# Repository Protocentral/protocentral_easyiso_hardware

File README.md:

ProtoCentral easyISO — Isolated Qwiic Adapter
==============================================

easyISO galvanically isolates a Qwiic / STEMMA QT I²C link — data and power — so a body-connected
sensor never shares a ground with a mains-powered computer.

* **I²C isolator:** TI ISO1640 (8-pin SOIC), bidirectional SDA/SCL, hot-swappable, up to 1.7 MHz
* **Isolated power:** MPS MIE1W0505BGLVH isolated DC-DC module, 3.3 V out (about 75 mA)
* **Connectors:** one Qwiic port and one 0.1" 4-pin header (SCL, SDA, VCC, GND) on each side
* **Pull-ups:** 10 kΩ on SDA and SCL, on both sides
* **Board:** 33 × 18.7 mm, 2-layer, 4 × M2 mounting holes

The voltage ratings above are the manufacturers' component ratings. easyISO is a development tool,
not a certified medical isolation barrier.

Repository contents
-------------------
* **/hardware** — KiCad project (`easyISO.kicad_pro`, `.kicad_sch`, `.kicad_pcb`) and the schematic
  PDF (`pc_easyiso_v1_schematic.pdf`)

Revisions
---------
| Revision | Date | Notes |
|---|---|---|
| v1 | 2026-08 | First release |

License Information
===================

Hardware
--------
**All hardware is released under the [CERN-OHL-P v2](https://ohwr.org/cern_ohl_p_v2.txt)** license.

This source describes Open Hardware and is licensed under the CERN-OHL-P v2.

You may redistribute and modify this documentation and make products using it under the terms of
the CERN-OHL-P v2 (https://cern.ch/cern-ohl). This documentation is distributed WITHOUT ANY EXPRESS
OR IMPLIED WARRANTY, INCLUDING OF MERCHANTABILITY, SATISFACTORY QUALITY AND FITNESS FOR A
PARTICULAR PURPOSE. Please see the CERN-OHL-P v2 for applicable conditions.

Documentation
-------------
**All documentation is released under [Creative Commons Share-alike 4.0 International](http://creativecommons.org/licenses/by-sa/4.0/).**

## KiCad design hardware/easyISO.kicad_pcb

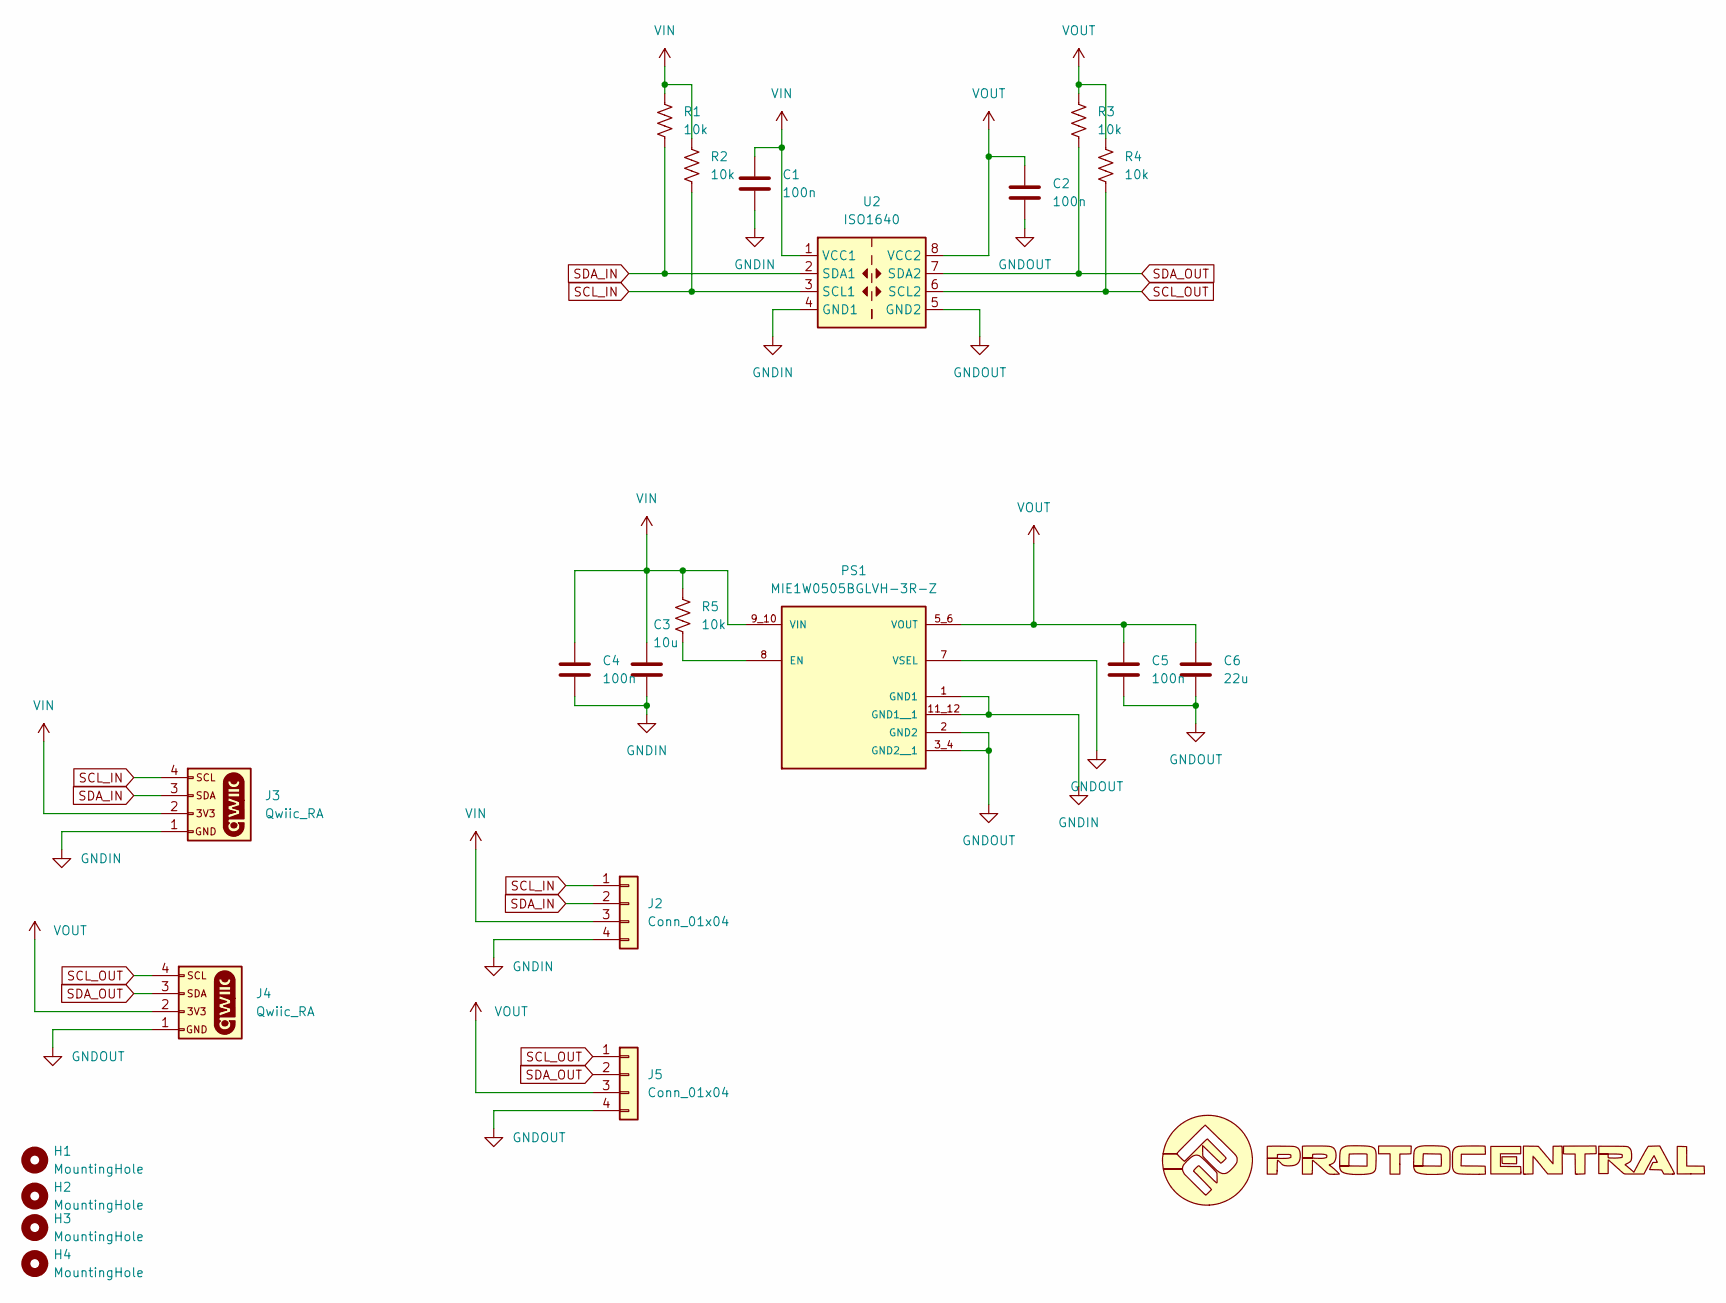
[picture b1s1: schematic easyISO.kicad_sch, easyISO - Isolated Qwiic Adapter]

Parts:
C1, C2, C4, C5: 100n; C_0402_1005Metric
C3: 10u; C_0805_2012Metric
C6: 22u; C_0805_2012Metric
H1, H2, H3, H4: MountingHole; MountingHole_2.2mm_M2
J2, J5: Conn_01x04; PinHeader_1x04_P2.54mm_Vertical
J3, J4: Qwiic_RA; JST_SH_SM04B-SRSS-TB_1x04-1MP_P1.00mm_Horizontal
PS1: MIE1W0505BGLVH-3R-Z; CONV_MIE1W0505BGLVH-3R-Z; PARTREV 0.8
R1, R2, R3, R4, R5: 10k; R_0402_1005Metric
U1: LOGO
U2: ISO1640; SOIC-8_3.9x4.9mm_P1.27mm

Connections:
GNDIN: C1.2, C3.2, C4.2, J2.4, J3.1, PS1.1 (GND1), PS1.11_12 (GND1__1), U2.4 (GND1)
GNDOUT: C2.2, C5.2, C6.2, J4.1, J5.4, PS1.2 (GND2), PS1.3_4 (GND2__1), PS1.7 (VSEL), U2.5 (GND2)
unnamed: PS1.8 (EN), R5.2
SCL_IN: J2.1, J3.4, R2.2, U2.3 (SCL1)
SCL_OUT: J4.4, J5.1, R4.2, U2.6 (SCL2)
SDA_IN: J2.2, J3.3, R1.2, U2.2 (SDA1)
SDA_OUT: J4.3, J5.2, R3.2, U2.7 (SDA2)
VIN: C1.1, C3.1, C4.1, J2.3, J3.2, PS1.9_10 (VIN), R1.1, R2.1, R5.1, U2.1 (VCC1)
VOUT: C2.1, C5.1, C6.1, J4.2, J5.3, PS1.5_6 (VOUT), R3.1, R4.1, U2.8 (VCC2)

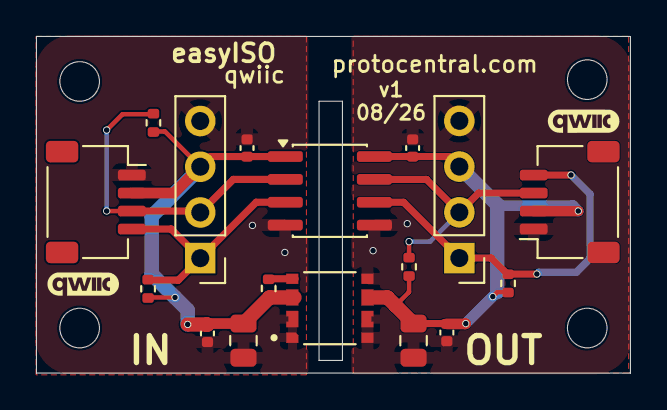
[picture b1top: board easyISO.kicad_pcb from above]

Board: 2 copper layers, 33.0 x 18.7 mm, 21 parts (0 on the bottom side), 9 nets.
